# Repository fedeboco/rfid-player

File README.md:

# RFID Music Player

System that provides an RFID card reader in order to select an album or track in an SD card, avoiding use of buttons or hard to use interfaces for elder people.

- Braille Compatibility.
- Designed for people with advanced age or hearing loss.
- SD Card support. 
- High volume. Volume control.
- Track and album control.
- Easy to setup new RFID cards by custom setup interface.

<p align="center">

## PCB

Custom PCB design for hand printing and soldering.
  
<p align="center">
  
## Schematic

Custom circuit design.
  
<p align="center">
  
## 3D Parts

Custom 3D printed enclosure for safe circuit install.

### Top
  
<p align="center">
  
### Bot  
  
<p align="center">
  
### Back

<p align="center">
  
### Decor

<p align="center">

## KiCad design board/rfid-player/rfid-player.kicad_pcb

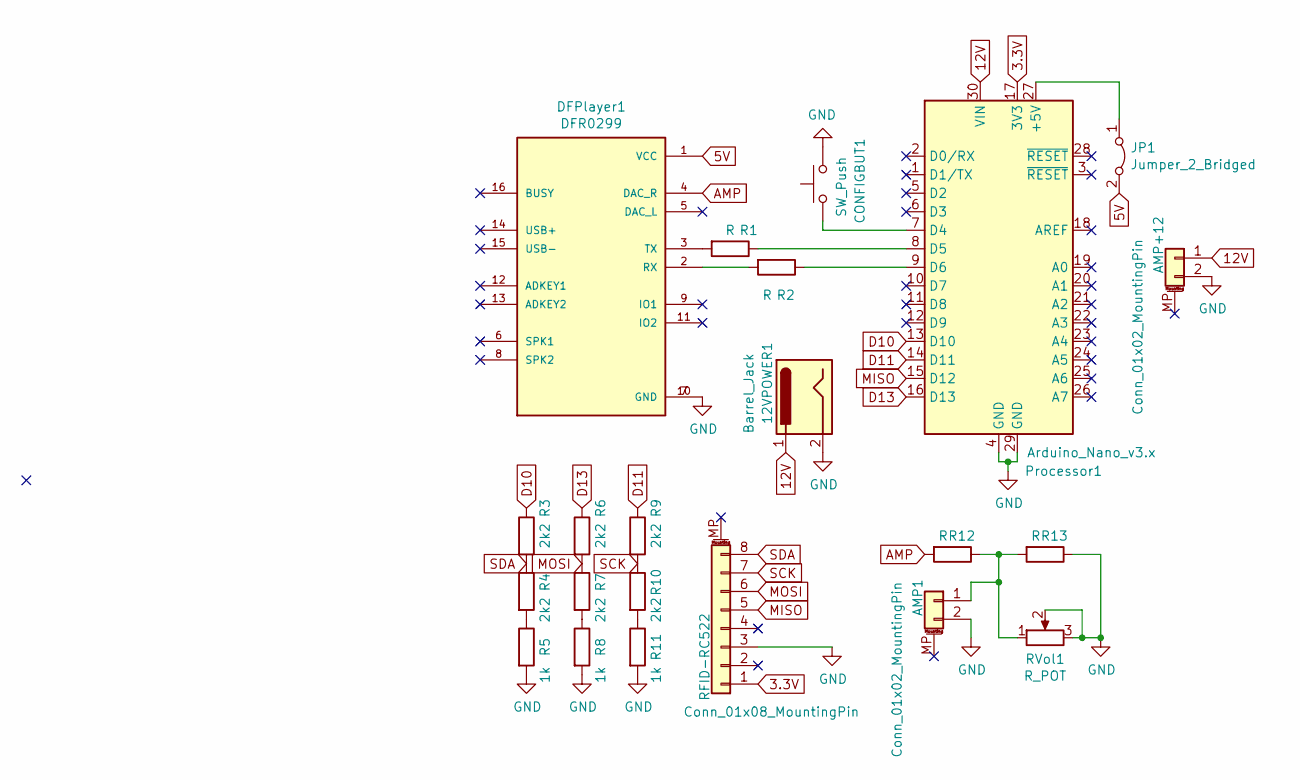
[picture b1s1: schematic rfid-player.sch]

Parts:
12VPOWER1: Barrel_Jack; BARREL_JACK
AMP1: Conn_01x02_MountingPin; Pin_Header_Straight_1x02_Pitch2.00mm
AMP+12: Conn_01x02_MountingPin; Pin_Header_Straight_1x02_Pitch2.00mm
CONFIGBUT1: SW_Push; SW_PUSH_6mm_h5mm
DFPlayer1: DFR0299; MODULE_DFR0299
JP1: Jumper_2_Bridged; R_Axial_DIN0204_L3.6mm_D1.6mm_P7.62mm_Horizontal
Processor1: Arduino_Nano_v3.x; Arduino_Nano_WithMountingHoles
R1, R2, R12, R13: R; R_Axial_DIN0204_L3.6mm_D1.6mm_P5.08mm_Horizontal
R3, R4, R6, R7, R9, R10: 2k2; R_Axial_DIN0204_L3.6mm_D1.6mm_P5.08mm_Horizontal
R5, R8, R11: 1k; R_Axial_DIN0204_L3.6mm_D1.6mm_P5.08mm_Horizontal
RFID-RC522: Conn_01x08_MountingPin; Pin_Header_Straight_1x08_Pitch2.00mm
RVol1: R_POT; Potentiometer_VishaySpectrol_148_149_Single_Horizontal

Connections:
3.3V: Processor1.17 (3V3), RFID-RC522.1
5V: DFPlayer1.1 (VCC), JP1.2 (B)
12V: 12VPOWER1.1, AMP+12.1, Processor1.30 (VIN)
AMP: DFPlayer1.4 (DAC_R), R12.2
D10: Processor1.13 (D10), R3.1
D11: Processor1.14 (D11), R9.1
D13: Processor1.16 (D13), R6.1
GND: 12VPOWER1.2, AMP1.2, AMP+12.2, CONFIGBUT1.2, DFPlayer1.7 (GND), DFPlayer1.10 (GND), Processor1.4 (GND), Processor1.29 (GND), R5.2, R8.2, R11.2, R13.1, RFID-RC522.3, RVol1.2, RVol1.3
MISO: Processor1.15 (D12), RFID-RC522.5
MOSI: R6.2, R7.1, RFID-RC522.6
unnamed: AMP1.1, R12.1, R13.2, RVol1.1
unnamed: CONFIGBUT1.1, Processor1.7 (D4)
unnamed: DFPlayer1.2 (RX), R2.2
unnamed: DFPlayer1.3 (TX), R1.2
unnamed: JP1.1 (A), Processor1.27 (+5V)
unnamed: Processor1.8 (D5), R1.1
unnamed: Processor1.9 (D6), R2.1
unnamed: R4.2, R5.1
unnamed: R7.2, R8.1
unnamed: R10.2, R11.1
SCK: R9.2, R10.1, RFID-RC522.7
SDA: R3.2, R4.1, RFID-RC522.8

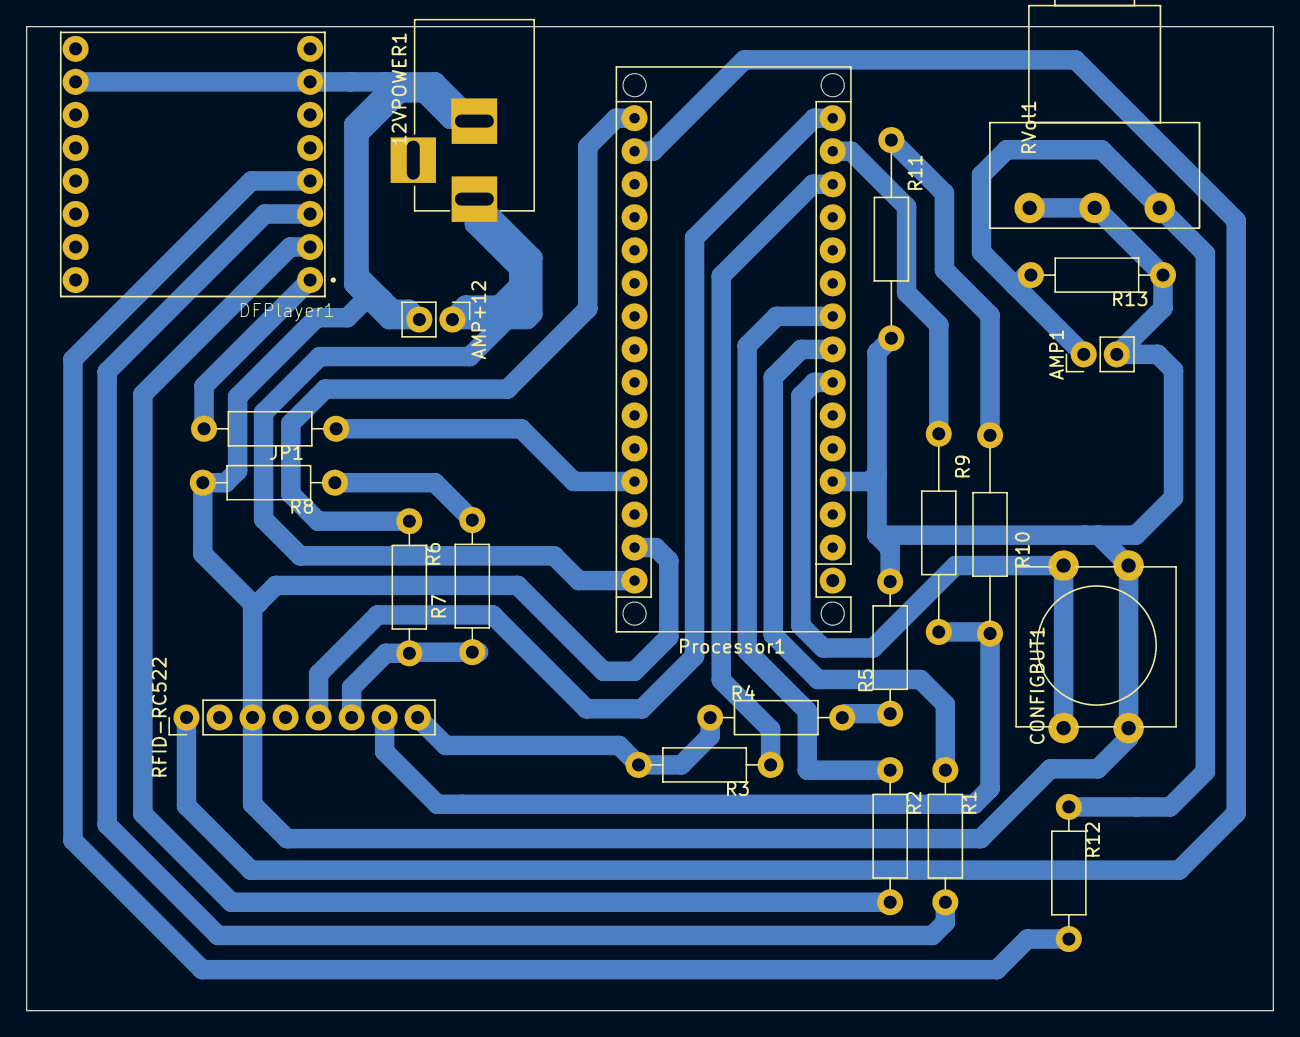
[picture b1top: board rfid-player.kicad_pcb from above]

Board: 2 copper layers, 95.9 x 75.7 mm, 22 parts (0 on the bottom side), 22 nets.

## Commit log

2020-11-09 Initial tests
2020-11-09 settings
2020-11-10 Created player class and migrated main functions
2020-11-10 Created card class for wrapping MFRC522
2020-11-12 EEPROM configuration
2020-11-13 EEPROM Cards ID read/write functional
2020-11-13 Fully functional
2020-11-18 next, play, folder improvements
2020-12-04 PCB Schematic and plot
2020-12-07 Board fixes
2020-12-07 fixed wrong resistor layout. logo inserted. reduced size.
2020-12-07 Added PCB PDF
2020-12-20 3D designs added
2021-01-15 added 3D files
2021-01-15 assets for readme
